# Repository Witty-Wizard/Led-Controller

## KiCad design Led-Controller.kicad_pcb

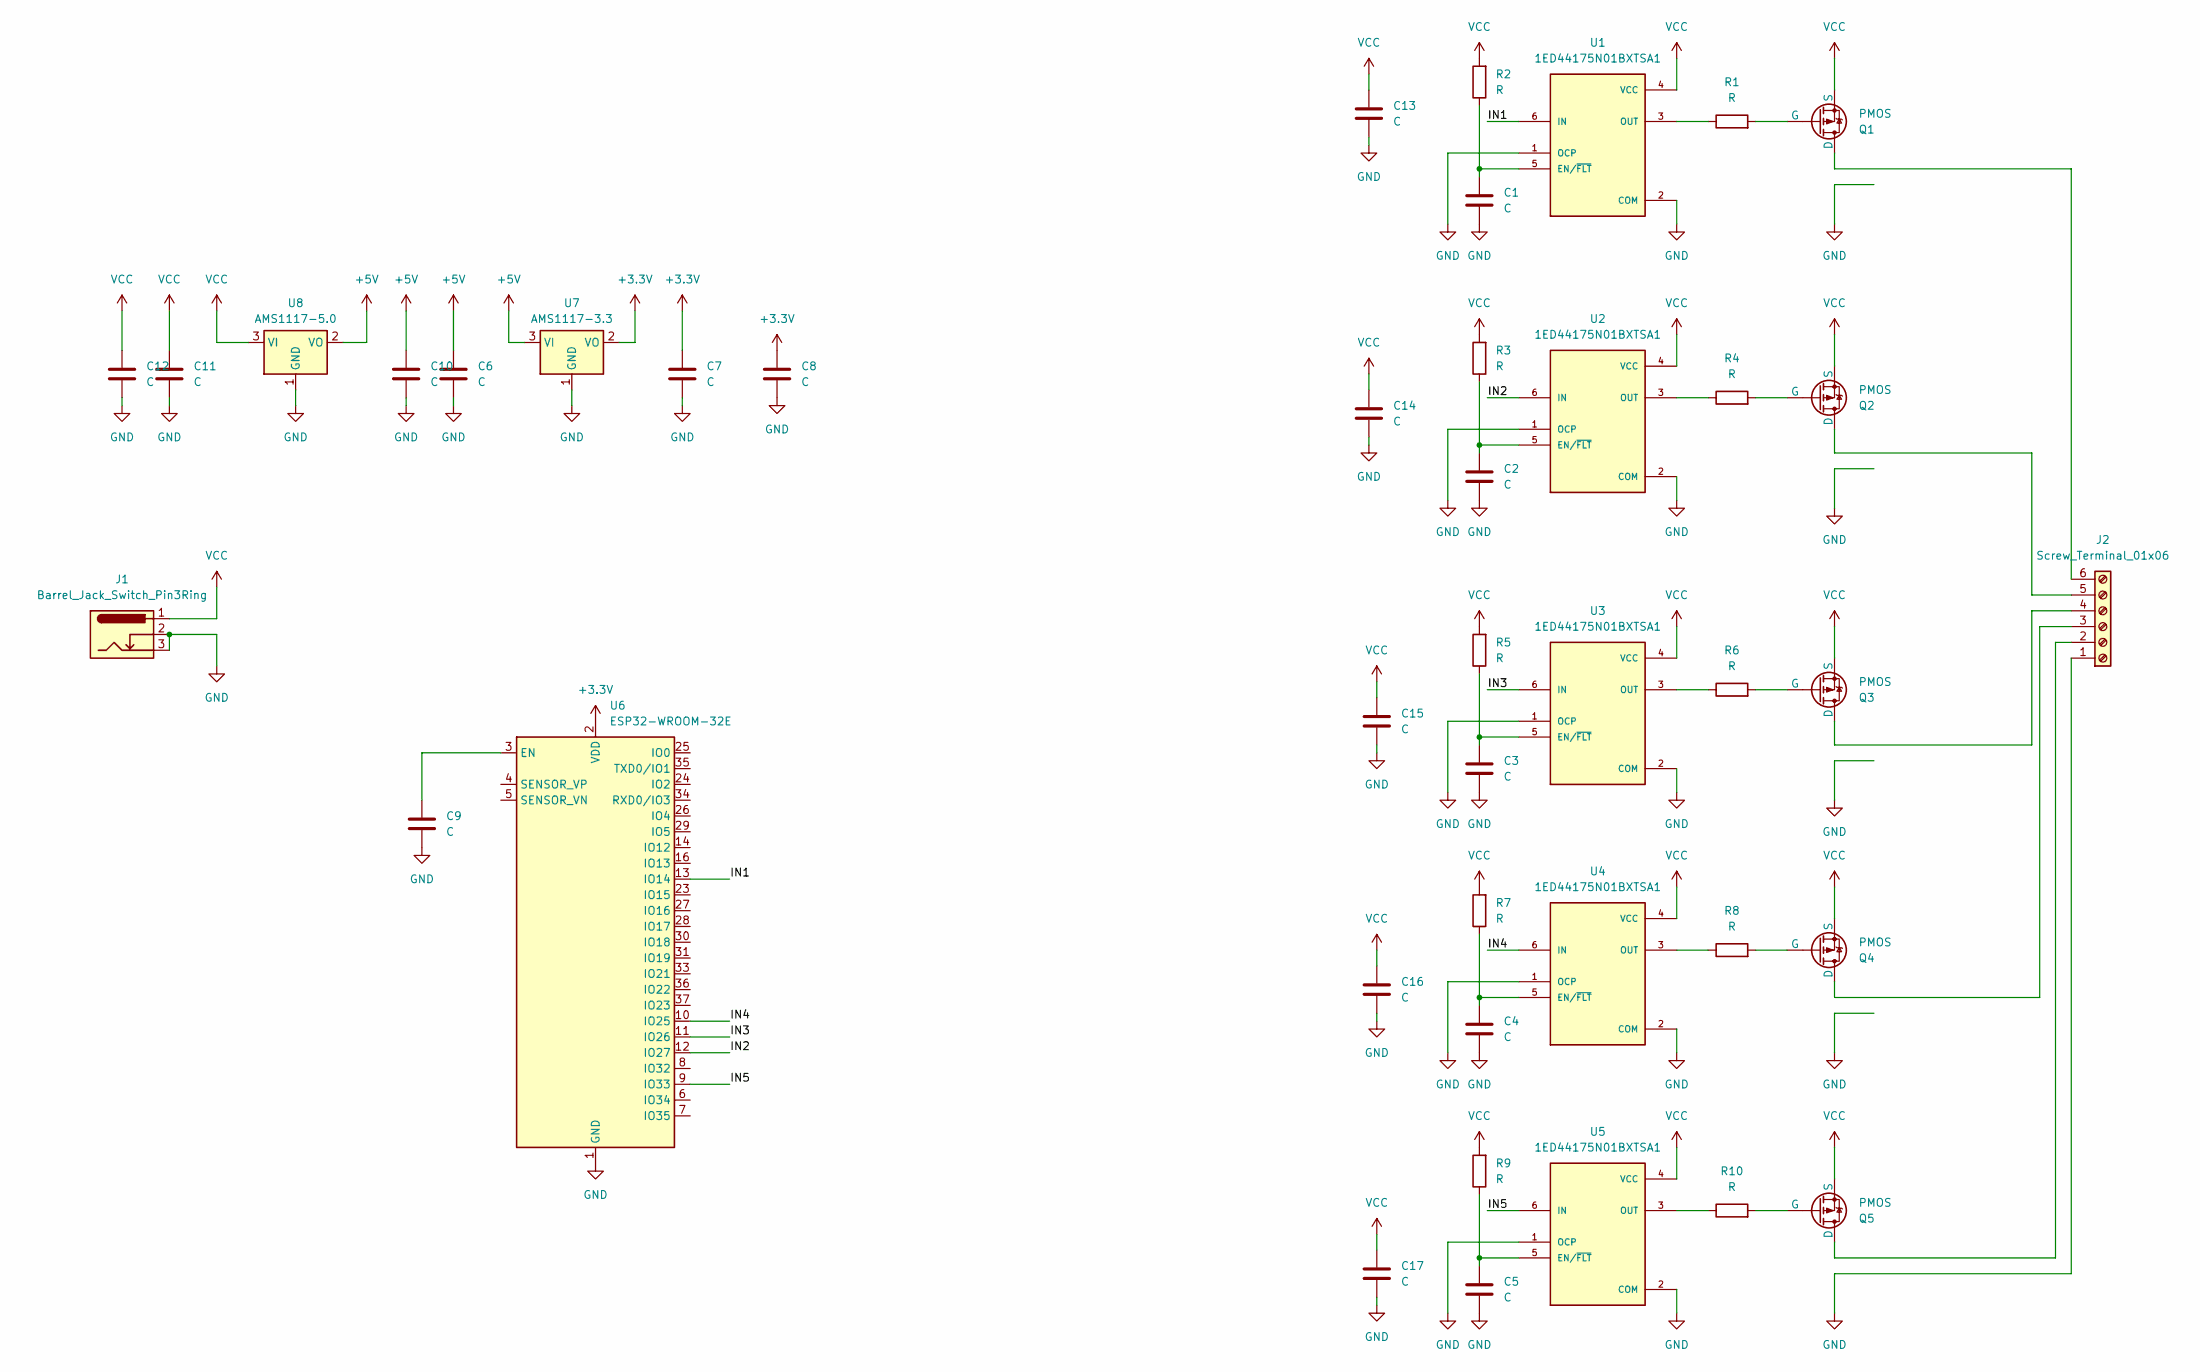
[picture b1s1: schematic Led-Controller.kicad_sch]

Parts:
C1, C2, C3, C4, C5, C6, C7, C8, C9, C10, C11, C12, C13, C14, C15, C16, C17: C; C_0805_2012Metric_Pad1.18x1.45mm_HandSolder
J1: Barrel_Jack_Switch_Pin3Ring; BarrelJack_GCT_DCJ200-10-A_Horizontal
J2: Screw_Terminal_01x06; TerminalBlock_bornier-6_P5.08mm
Q1, Q2, Q3, Q4, Q5: PMOS; BSZ180P03
R1, R2, R3, R4, R5, R6, R7, R8, R9, R10: R; R_0805_2012Metric_Pad1.20x1.40mm_HandSolder
U1, U2, U3, U4, U5: 1ED44175N01BXTSA1; PARTREV 1.0
U6: ESP32-WROOM-32E; ESP32-WROOM-32D
U7: AMS1117-3.3; SOT-223-3_TabPin2
U8: AMS1117-5.0; SOT-223-3_TabPin2

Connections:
+3.3V: C7.1, C8.1, U6.2 (VDD), U7.2 (VO)
+5V: C6.1, C10.1, U7.3 (VI), U8.2 (VO)
/IN1: U1.6 (IN), U6.13 (IO14)
/IN2: U2.6 (IN), U6.12 (IO27)
/IN3: U3.6 (IN), U6.11 (IO26)
/IN4: U4.6 (IN), U6.10 (IO25)
/IN5: U5.6 (IN), U6.9 (IO33)
GND: C1.2, C2.2, C3.2, C4.2, C5.2, C6.2, C7.2, C8.2, C9.2, C10.2, C11.2, C12.2, C13.2, C14.2, C15.2, C16.2, C17.2, J1.2, J1.3, J2.1, U1.1 (OCP), U1.2 (COM), U2.1 (OCP), U2.2 (COM), U3.1 (OCP), U3.2 (COM), U4.1 (OCP), U4.2 (COM), U5.1 (OCP), U5.2 (COM), U6.1 (GND), U6.15 (GND), U6.38 (GND), U6.39 (GND), U7.1 (GND), U8.1 (GND)
unnamed: J2.2, Q5.1 (D)
unnamed: J2.3, Q4.1 (D)
unnamed: J2.4, Q3.1 (D)
unnamed: J2.5, Q2.1 (D)
unnamed: J2.6, Q1.1 (D)
unnamed: Q1.2 (G), R1.2
unnamed: Q2.2 (G), R4.2
unnamed: Q3.2 (G), R6.2
unnamed: Q4.2 (G), R8.2
unnamed: Q5.2 (G), R10.2
unnamed: C1.1, R2.1, U1.5 (EN/~FLT)
unnamed: R1.1, U1.3 (OUT)
unnamed: C2.1, R3.1, U2.5 (EN/~FLT)
unnamed: R4.1, U2.3 (OUT)
unnamed: C3.1, R5.1, U3.5 (EN/~FLT)
unnamed: R6.1, U3.3 (OUT)
unnamed: C4.1, R7.1, U4.5 (EN/~FLT)
unnamed: R8.1, U4.3 (OUT)
unnamed: C5.1, R9.1, U5.5 (EN/~FLT)
unnamed: R10.1, U5.3 (OUT)
unnamed: C9.1, U6.3 (EN)
VCC: C11.1, C12.1, C13.1, C14.1, C15.1, C16.1, C17.1, J1.1, Q1.3 (S), Q2.3 (S), Q3.3 (S), Q4.3 (S), Q5.3 (S), R2.2, R3.2, R5.2, R7.2, R9.2, U1.4 (VCC), U2.4 (VCC), U3.4 (VCC), U4.4 (VCC), U5.4 (VCC), U8.3 (VI)

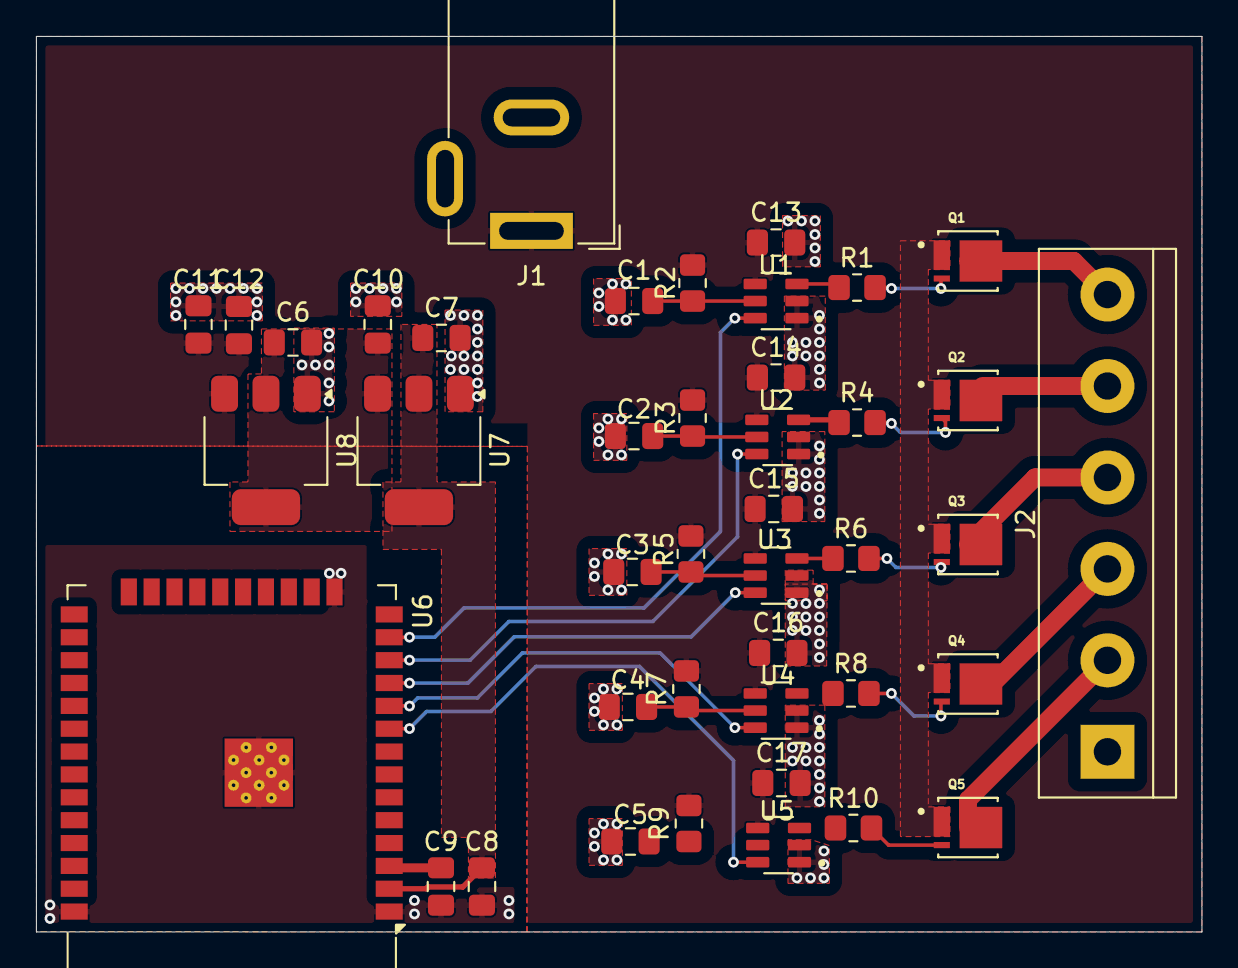
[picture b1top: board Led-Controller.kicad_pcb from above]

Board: 2 copper layers, 64.8 x 49.8 mm, 42 parts (0 on the bottom side), 30 nets.

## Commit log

2024-07-17 Made Schemetics
2024-09-29 Final PCB
2024-09-29 added gerber generation workflow
2024-09-29 fixed the workflow
